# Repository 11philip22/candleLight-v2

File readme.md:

# candleLight USB-to-CAN Adapter

A KiCad **USB-to-CAN adapter** built around the **STM32F072** microcontroller and **TJA1051TK-3** CAN transceiver. USB-C connects to the host, while a screw terminal exposes CAN_H, CAN_L, and GND. The board includes selectable 120 Ω CAN termination and headers for SWD, USART, and SPI.

| Top — USB connector side | Bottom — through-hole models hidden |
| :---: | :---: |
|  |  |

## Project files

| File | Description |
| --- | --- |
| [candleLight.kicad_pro](candleLight.kicad_pro) | KiCad project |
| [candleLight.kicad_sch](candleLight.kicad_sch) | Schematic |
| [candleLight.kicad_pcb](candleLight.kicad_pcb) | Two-layer PCB, revision V2.1, 1.2 mm thick |
| [lib/](lib/) | Custom symbols, footprints, and 3D models (Git submodule) |
| [production/](production/) | Fabrication archive, bill of materials, component positions, and netlist |

## Open in KiCad

Initialize the library submodule before opening the project:

```sh
git submodule update --init --recursive
```

Open `candleLight.kicad_pro` in KiCad 9 or newer, with the standard symbol, footprint, and 3D-model libraries installed. The board references `KICAD9_3DMODEL_DIR`; when using a newer KiCad version, set that path variable to the installed 3D-model library directory if models are missing.

## Board revisions

### [V2.1](https://github.com/11philip22/candleLight-v2/tree/v2.1)

- Reworked decoupling capacitors.
- Added NRST and BOOT0 controls, an NRST pull-up, and a higher-value BOOT0 resistor.
- Added selectable CAN termination and a BOOT0 selection header.
- Changed the crystal to a JLCPCB basic part.
- Improved the SWD header and added USART and SPI headers.
- Upgraded the CAN transceiver from TJA1051-3 to TJA1051TK-3.
- Added a Schottky diode between VBUS and V5+ and ESD protection on the USB lines.

### [V2](https://github.com/11philip22/candleLight-v2/tree/v2)

- Changed the voltage regulator and crystal.
- Switched to USB-C.
- Replaced the Tag-Connect connector with standard pin headers.
- Replaced the VGA-style CAN connector with a Phoenix screw terminal.

## Board photos

### [V2.1](https://github.com/11philip22/candleLight-v2/tree/v2.1)

| Assembly photo 1 | Assembly photo 2 | Assembly photo 3 |
| :---: | :---: | :---: |
|  |  |  |

### [V2](https://github.com/11philip22/candleLight-v2/tree/v2)

| Assembly photo 1 | Assembly photo 2 | Assembly photo 3 |
| :---: | :---: | :---: |
|  |  |  |

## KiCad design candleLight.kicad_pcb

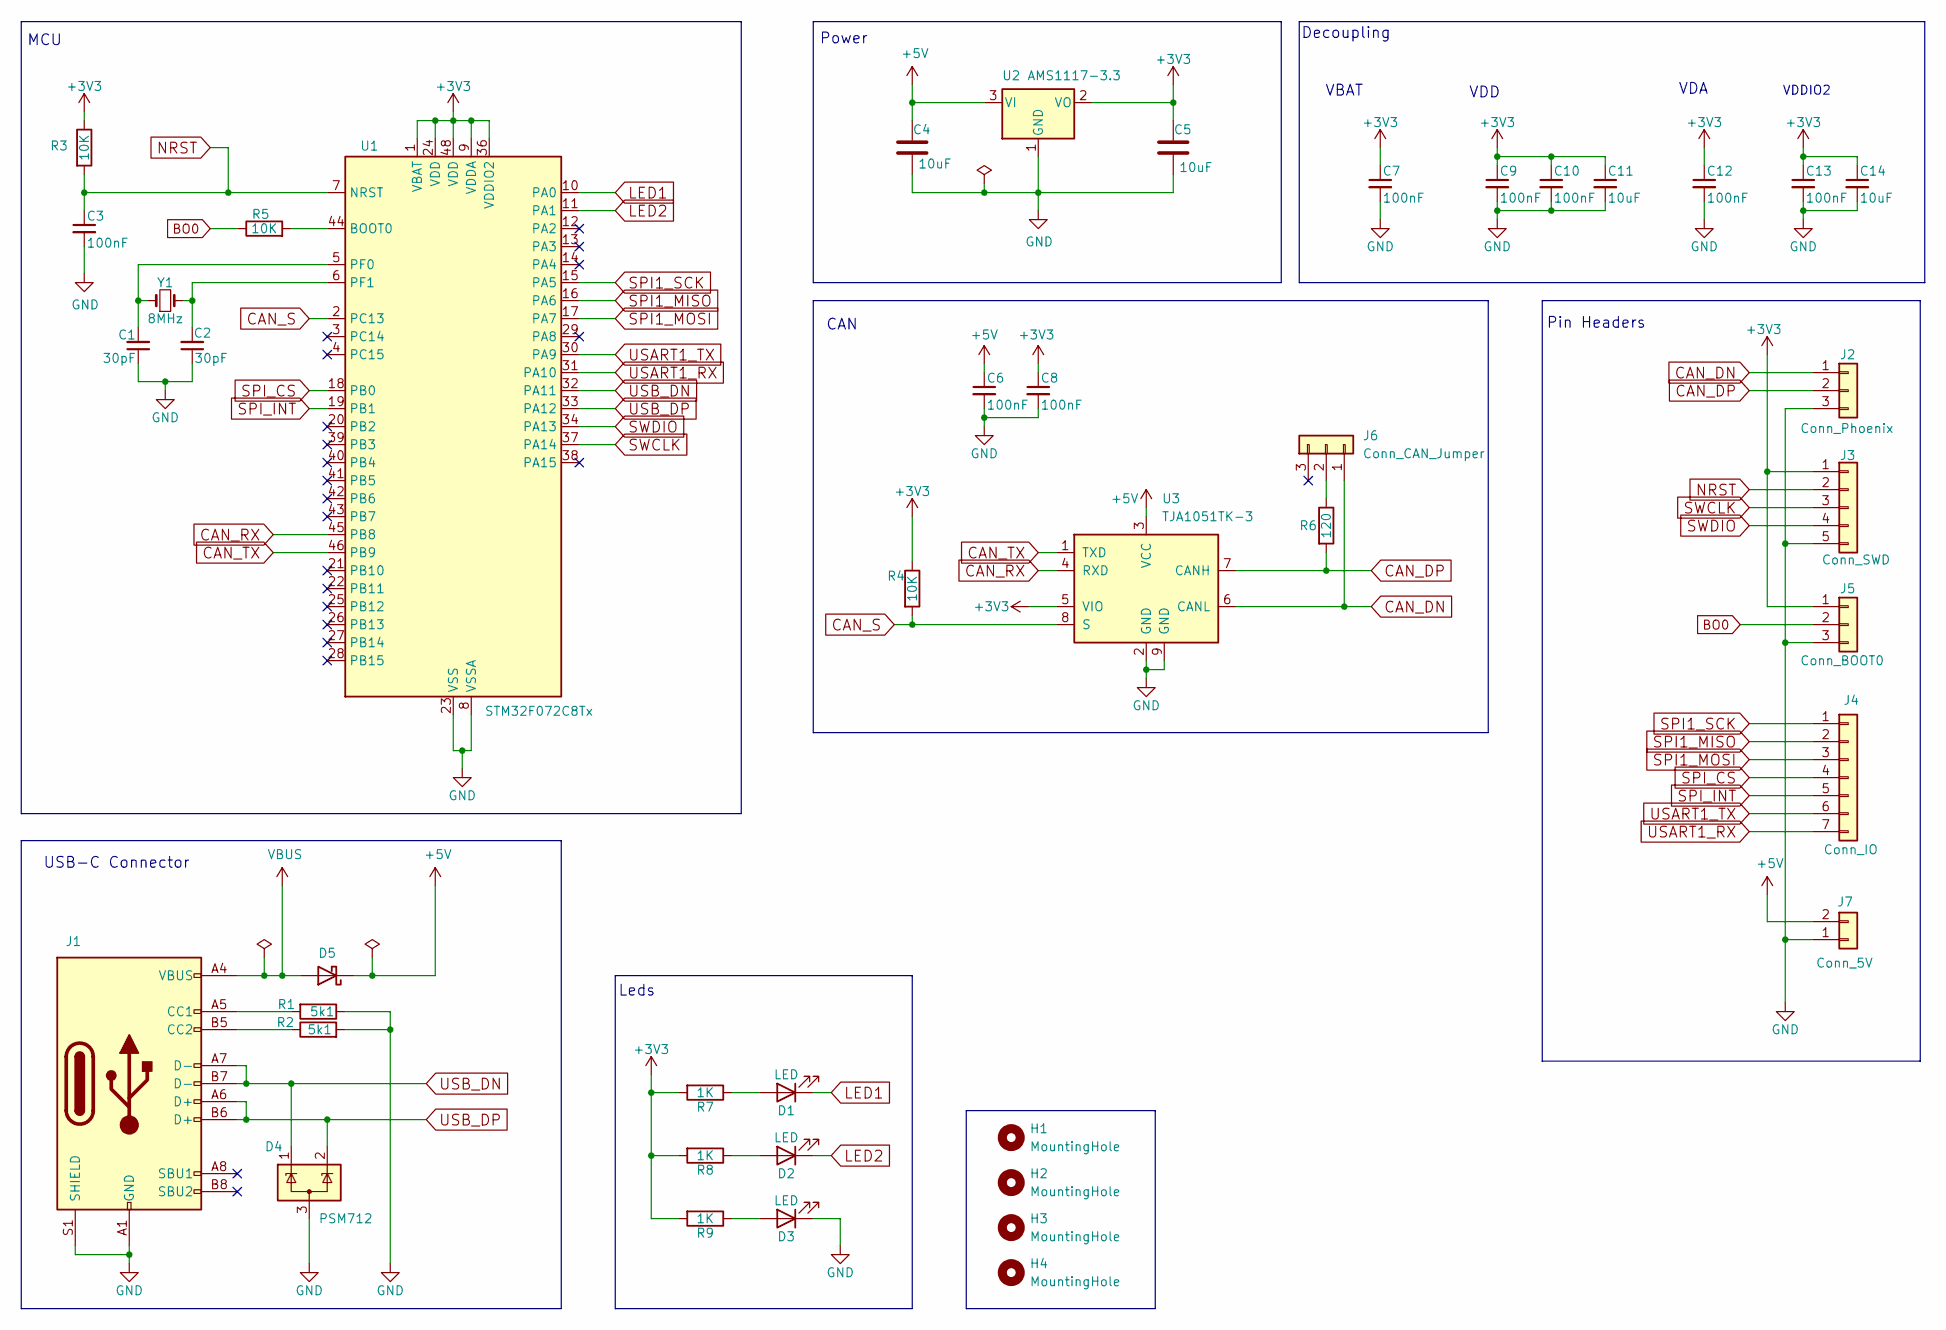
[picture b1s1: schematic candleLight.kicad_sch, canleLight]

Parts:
C1, C2: 30pF; C_0603_1608Metric; LCSC C1658
C3, C6, C7, C8, C9, C10, C12, C13: 100nF; C_0603_1608Metric; LCSC C14663
C4, C5, C11, C14: 10uF; C_0805_2012Metric; LCSC C15850
D1, D2: LED; LED_0603_1608Metric; LCSC C2290
D3: LED; LED_0603_1608Metric; LCSC C2286
D4: PSM712; SOT-23; LCSC C32677
D5: D_SOD-123; LCSC C8598
H1, H2, H3, H4: MountingHole; MountingHole_2.1mm
J1: USB_C_Receptacle_USB2.0; USB_C_Receptacle_HRO_TYPE-C-31-M-12; LCSC C165948
J2: Conn_Phoenix; TerminalBlock_Phoenix_MKDS-1,5-3-5.08_1x03_P5.08mm_Horizont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; LCSC C474951
J3: Conn_SWD; PinHeader_1x05_P2.54mm_Vertical; LCSC C32713271
J4: Conn_IO; PinHeader_1x07_P2.54mm_Vertical; LCSC C32713273
J5: Conn_BOOT0; PinHeader_1x03_P2.54mm_Vertical; LCSC C32713269
J6: Conn_CAN_Jumper; PinHeader_1x03_P2.54mm_Vertical; LCSC C32713269
J7: Conn_5V; PinHeader_1x02_P2.54mm_Vertical; LCSC C32713268
R1, R2: 5k1; R_0603_1608Metric; LCSC C23186
R3, R4, R5: 10K; R_0603_1608Metric; LCSC C25804
R6: 120; R_0603_1608Metric; LCSC C22787
R7, R8, R9: 1K; R_0603_1608Metric; LCSC C21190
U1: STM32F072C8Tx; LQFP-48_7x7mm_P0.5mm; LCSC C80488
U2: AMS1117-3.3; SOT-223-3_TabPin2; LCSC C6186
U3: TJA1051TK-3; DFN-8-1EP_3x3mm_P0.65mm_EP1.55x2.4mm; LCSC C2875699
Y1: 8MHz; Crystal_SMD_Abracon_ABM3-2Pin_5.0x3.2mm; LCSC C115962

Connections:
+3V3: C5.1, C7.1, C8.1, C9.1, C10.1, C11.1, C12.1, C13.1, C14.1, J3.1, J5.1, R3.1, R4.1, R7.2, R8.2, R9.2, U1.1 (VBAT), U1.9 (VDDA), U1.24 (VDD), U1.36 (VDDIO2), U1.48 (VDD), U2.2 (VO), U3.5 (VIO)
+5V: C4.1, C6.1, D5.1 (K), J7.2 (Pin_1), U2.3 (VI), U3.3 (VCC)
BO0: J5.2, R5.1
CAN_DN: J2.1, J6.1 (Pin_3), U3.6 (CANL)
CAN_DP: J2.2, R6.2, U3.7 (CANH)
CAN_RX: U1.45 (PB8), U3.4 (RXD)
CAN_S: R4.2, U1.2 (PC13), U3.8 (S)
CAN_TX: U1.46 (PB9), U3.1 (TXD)
GND: C1.1, C2.1, C3.2, C4.2, C5.2, C6.2, C7.2, C8.2, C9.2, C10.2, C11.2, C12.2, C13.2, C14.2, D3.1 (K), D4.3 (A), J1.A1 (GND), J1.A12 (GND), J1.B1 (GND), J1.B12 (GND), J1.S1 (SHIELD), J2.3, J3.5, J5.3, J7.1 (Pin_2), R1.1, R2.2, U1.8 (VSSA), U1.23 (VSS), U1.35 (VSS), U1.47 (VSS), U2.1 (GND), U3.2 (GND), U3.9 (GND)
LED1: D1.1 (K), U1.10 (PA0)
LED2: D2.1 (K), U1.11 (PA1)
NRST: C3.1, J3.2, R3.2, U1.7 (NRST)
unnamed: D1.2 (A), R7.1
unnamed: D2.2 (A), R8.1
unnamed: D3.2 (A), R9.1
unnamed: J1.A5 (CC1), R1.2
unnamed: J1.B5 (CC2), R2.1
unnamed: J6.2, R6.1
unnamed: R5.2, U1.44 (BOOT0)
unnamed: C1.2, U1.5 (PF0), Y1.1
unnamed: C2.2, U1.6 (PF1), Y1.2
SPI1_MISO: J4.2, U1.16 (PA6)
SPI1_MOSI: J4.3, U1.17 (PA7)
SPI1_SCK: J4.1, U1.15 (PA5)
SPI_CS: J4.4, U1.18 (PB0)
SPI_INT: J4.5, U1.19 (PB1)
SWCLK: J3.3, U1.37 (PA14)
SWDIO: J3.4, U1.34 (PA13)
USART1_RX: J4.7, U1.31 (PA10)
USART1_TX: J4.6, U1.30 (PA9)
USB_DN: D4.1 (K), J1.A7 (D-), J1.B7 (D-), U1.32 (PA11)
USB_DP: D4.2 (K), J1.A6 (D+), J1.B6 (D+), U1.33 (PA12)
VBUS: D5.2 (A), J1.A4 (VBUS), J1.A9 (VBUS), J1.B4 (VBUS), J1.B9 (VBUS)

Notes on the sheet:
MCU
Leds
VDD
USB-C Connector
VDDIO2
VBAT
VDA
Power
Pin Headers
CAN
Decoupling

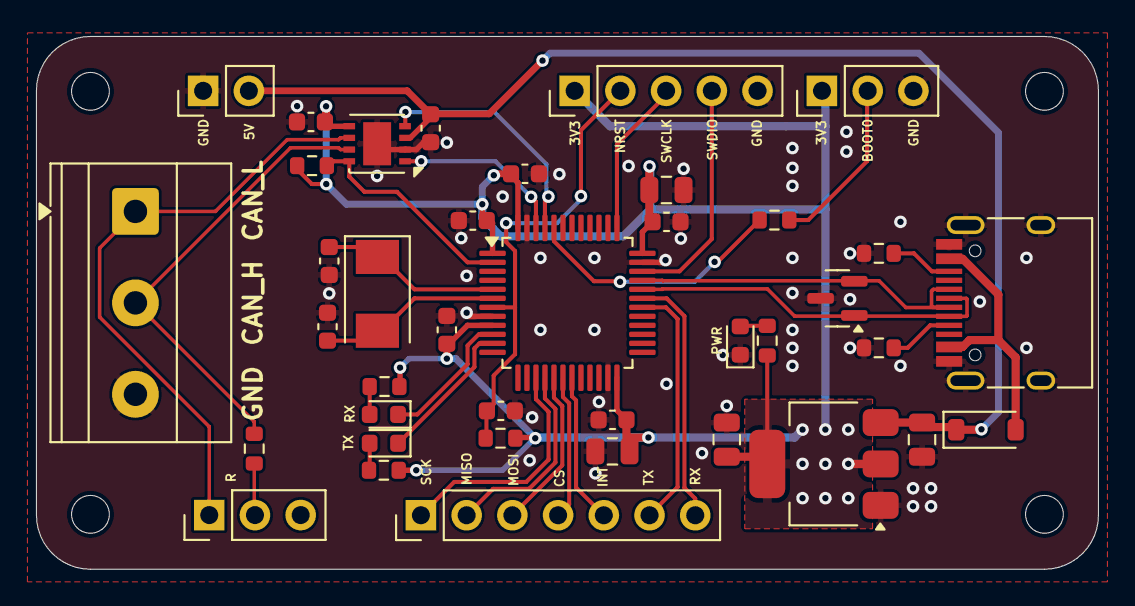
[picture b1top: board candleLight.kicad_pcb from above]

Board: 2 copper layers, 59.0 x 29.6 mm, 43 parts (0 on the bottom side), 33 nets.

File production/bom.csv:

Designator,Footprint,Quantity,Value,LCSC Part #
"C1, C2",0603,2,30pF,C1658
"C10, C12, C13, C3, C6, C7, C8, C9",0603,8,100nF,C14663
"C11, C14, C4, C5",0805,4,10uF,C15850
"D1, D2",0603,2,LED,C2290
D3,0603,1,LED,C2286
D4,SOT-23,1,PSM712,C32677
D5,D_SOD-123,1,~,C8598
J1,USB_C_Receptacle_HRO_TYPE-C-31-M-12,1,USB_C_Receptacle_USB2.0,C165948
J2,"TerminalBlock_Phoenix_MKDS-1,5-3-5.08_1x03_P5.08mm_Horizontal",1,Conn_Phoenix,C474951
J3,PinHeader_1x05_P2.54mm_Vertical,1,Conn_SWD,C32713271
J4,PinHeader_1x07_P2.54mm_Vertical,1,Conn_IO,C32713273
J5,PinHeader_1x03_P2.54mm_Vertical,1,Conn_BOOT0,C32713269
J6,PinHeader_1x03_P2.54mm_Vertical,1,Conn_CAN_Jumper,C32713269
J7,PinHeader_1x02_P2.54mm_Vertical,1,Conn_5V,C32713268
"R1, R2",0603,2,5k1,C23186
"R3, R4, R5",0603,3,10K,C25804
R6,0603,1,120,C22787
"R7, R8, R9",0603,3,1K,C21190
U1,LQFP-48_7x7mm_P0.5mm,1,STM32F072C8Tx,C80488
U2,SOT-223-3_TabPin2,1,AMS1117-3.3,C6186
U3,DFN-8-1EP_3x3mm_P0.65mm_EP1.55x2.4mm,1,TJA1051TK-3,C2875699
Y1,Crystal_SMD_Abracon_ABM3-2Pin_5.0x3.2mm,1,8MHz,C115962

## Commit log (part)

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2025-10-03 kicad 9
2025-10-04 usb-c
2025-10-04 remove eagle files
2025-10-05 schematic
2025-10-07 v2 ready
2025-10-07 production :)
2025-10-11 update schematic
2025-10-11 remove backups
2025-10-11 lib submodule
2025-10-11 LCSC
2025-10-17 inital board
2025-10-19 layout
2025-10-20 update silkscreen
2025-10-21 uppdate silkscreen and SPI header
2025-10-21 production
2025-10-21 update load caps
2025-10-21 add datasheet
2025-10-21 add version 2 images
2025-10-21 add v2.1 images
2025-10-23 fix silkscreen
2025-10-30 update photos
